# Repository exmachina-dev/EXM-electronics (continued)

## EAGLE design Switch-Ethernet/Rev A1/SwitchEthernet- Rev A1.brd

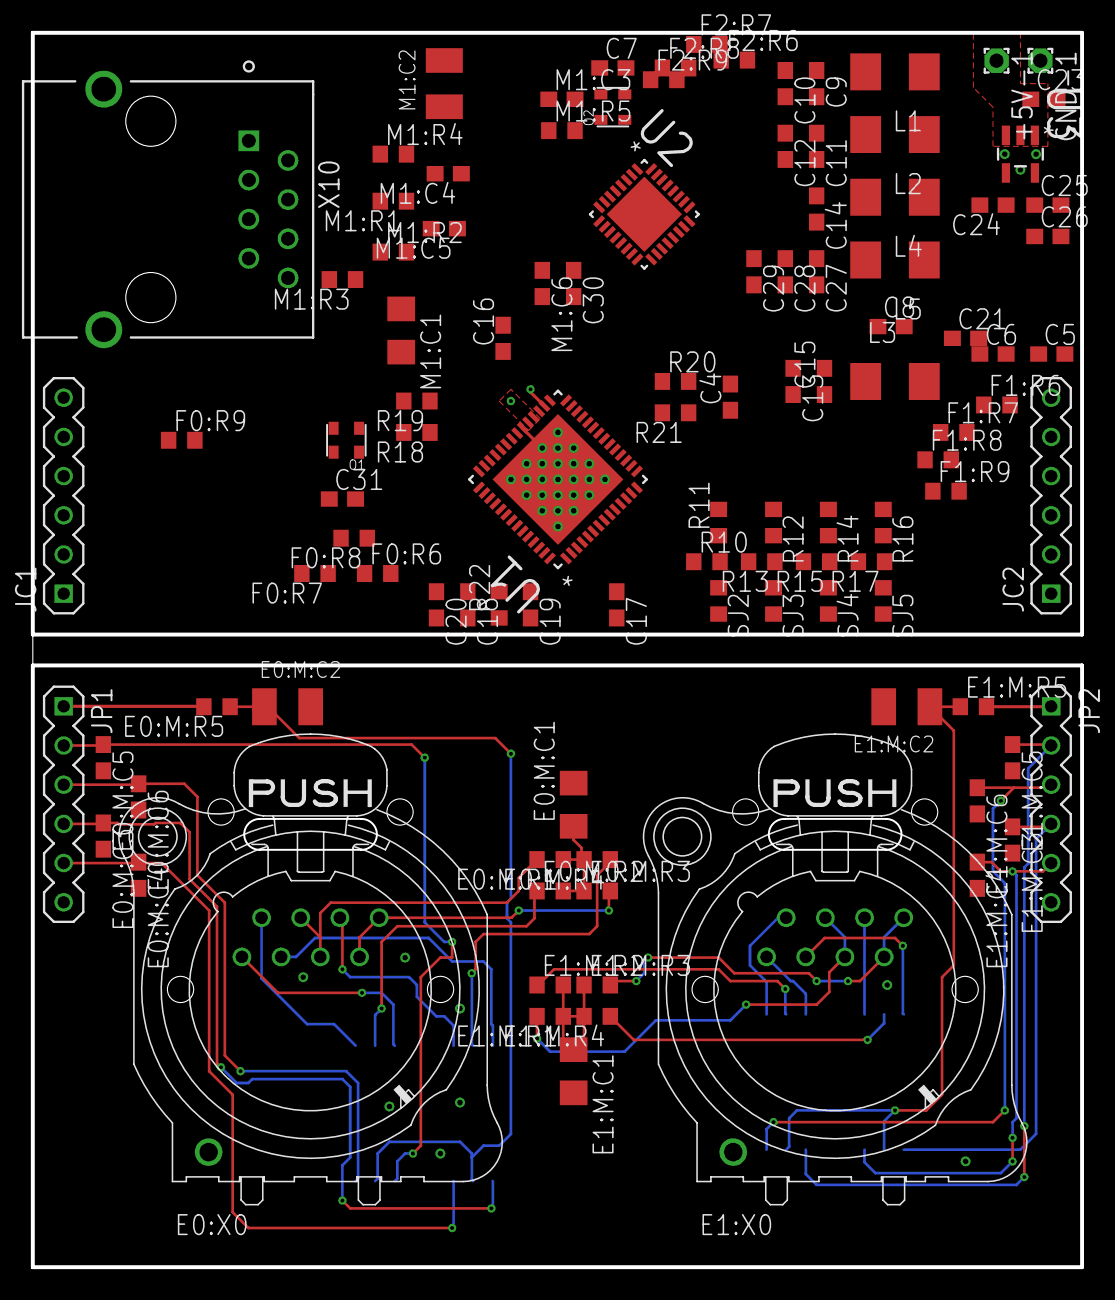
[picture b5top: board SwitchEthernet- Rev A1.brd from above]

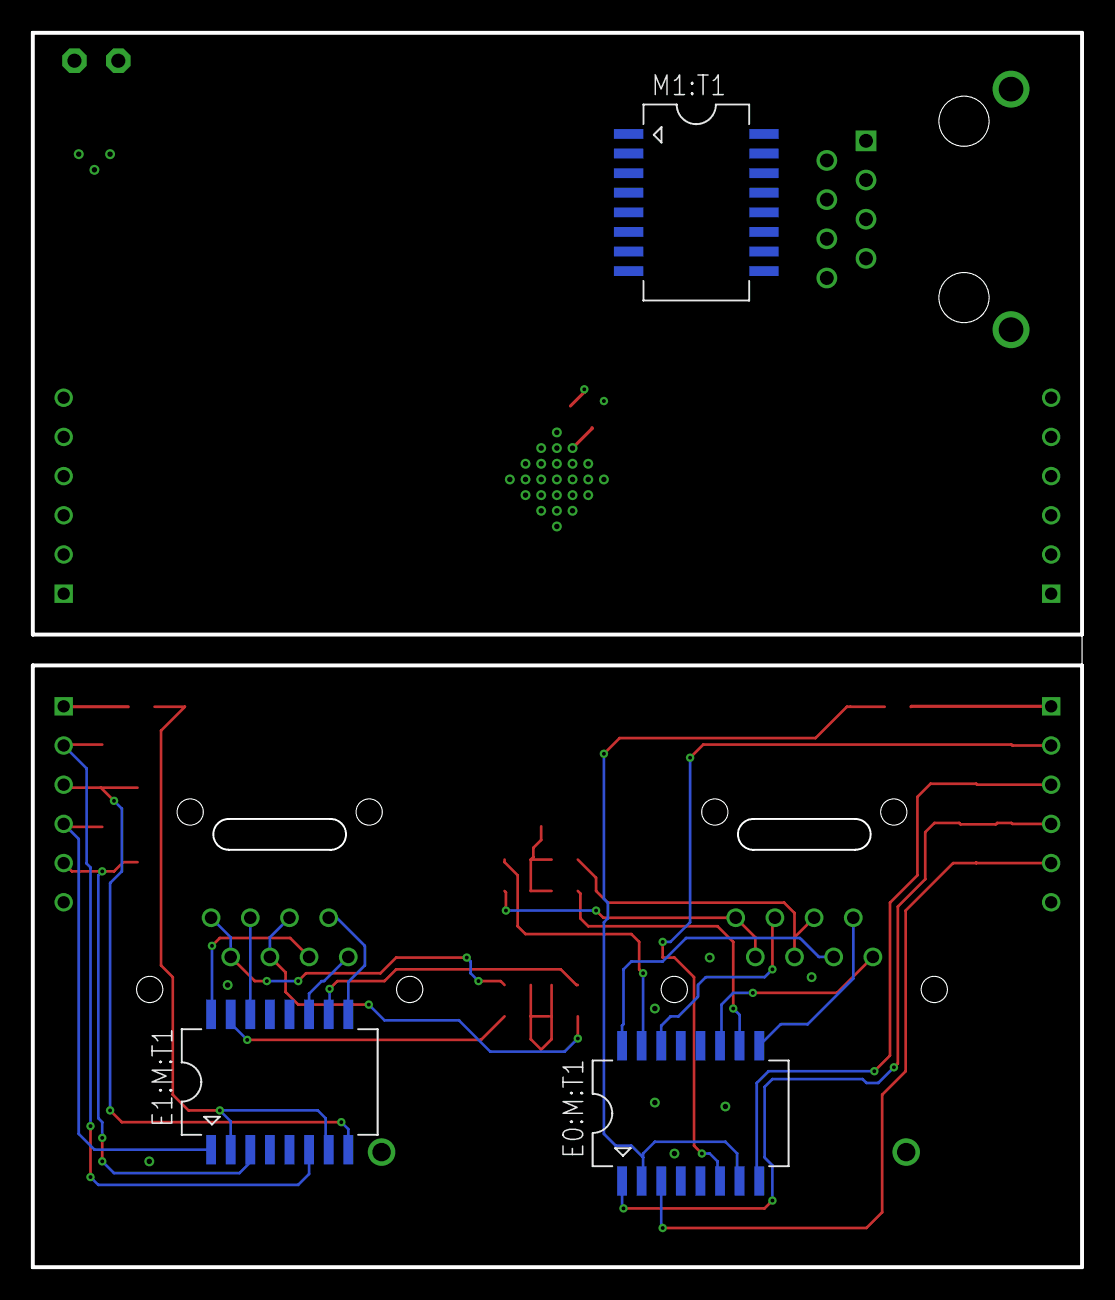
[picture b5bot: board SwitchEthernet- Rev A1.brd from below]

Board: 4 copper layers, 68.0 x 80.0 mm, 111 parts (3 on the bottom side), 90 nets.

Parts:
+5V-1: WIREPAD1,6/0,9; 1,6/0,9
C4, C9, C10, C11, C12, C13, C14, C15, C18: 4.7uF, 6.3V, 20%; C0603
C5, C6, C8, C16, C17, C19, C20: 0.1uF, 16V, 10%; C0603
C7: 0.1uF; C0603
C21, C31: 0.01uF, 6V, 10%; C0603
C23: 1uF, 16V; C0603
C24: 10nF, 50V; C0603
C25, C27: 4.7uF, 6.3V; C0603
C26, C28, C29, C30: 0.1uF, 16V; C0603
E0:M:C1, E1:M:C1: 1000pF, 2kV; C1206
E0:M:C2, E1:M:C2: .022uF; SMC_B
E0:M:C3, E0:M:C4, E0:M:C5, E0:M:C6, E1:M:C3, E1:M:C4, E1:M:C5, E1:M:C6: 15pF, 50V; C0603
E0:M:R1, E0:M:R2, E0:M:R3, E0:M:R4, E1:M:R1, E1:M:R2, E1:M:R3, E1:M:R4: 75; R0603
E0:M:R5, E1:M:R5: 10, 1/8W, 1%; R0603
E0:M:T1, E1:M:T1: 749010012
E0:X0, E1:X0: NE8FAV
F0:R6, F0:R7, F0:R8, F0:R9, F1:R6, F1:R7, F1:R8, F1:R9, F2:R6, F2:R7, F2:R8, F2:R9: 49.9, 1/8W, 1%; R0603
GND-1: WIREPAD1,6/0,9; 1,6/0,9
JC1, JC2: 1X06
JP1, JP2: 1X06
L1, L2, L3, L4, L5: 2.0A/0.05 DCR; L4532M
M1:C1: 1000pF, 2kV; C1206
M1:C2: .022uF; SMC_B
M1:C3, M1:C4, M1:C5, M1:C6: 15pF, 50V; C0603
M1:R1, M1:R2, M1:R3, M1:R4: 75; R0603
M1:R5: 10, 1/8W, 1%; R0603
M1:T1: 749010012
O1, O2: 25MHz; ADSM
R10, R11, R12, R13, R14, R15, R16, R17, R18, R19, R20, R21: 10K, 1/10W, 1%; R0603
R22: 12K4, 1%; R0603
SJ2, SJ3, SJ4, SJ5: O, DNI; R0603
U1: LAN9303-ABZJ; QFN50P800X800X100-57N
U2: LAN8710AI-EZK; QFN50P500X500X100-33N
U3: LP2992IM5-3.3; SOT95P284X122-5N
X10: 85505-5113; MOLEX_85505-5113

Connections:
+3V3: C4.1, C5.1, C6.1, C7.1, C8.1, C21.1, C25.1, C26.1, C31.1, L1.1, L2.1, L4.1, L5.1, O1.4, O2.4, R10.1, R12.1, R14.1, R16.1, R18.2, R19.2, R20.2, U1.9, U1.15, U1.23, U1.30, U1.32, U1.33, U3.5
+5V: +5V-1.1, C23.1, U3.1, U3.3
AVDD: C27.1, C28.1, C29.1, F2:R6.2, F2:R7.2, F2:R8.2, F2:R9.2, L5.2, M1:R5.2, U2.1, U2.27
DUPLEX_POL_0: R16.2, R17.1, SJ5.1
E0:M:N$1: E0:M:C2.+, E0:M:R5.1, E0:M:T1.2, E0:M:T1.7
E0:M:N$2: E0:M:R2.1, E0:M:T1.10
E0:M:N$3: E0:M:R4.1, E0:M:T1.15
E0:M:N$8: E0:M:C1.1, E0:M:R1.1, E0:M:R2.2, E0:M:R3.1, E0:M:R4.2
E0:N$1: E0:M:T1.11, E0:X0.1
E0:N$2: E0:M:T1.9, E0:X0.2
E0:N$3: E0:M:T1.16, E0:X0.3
E0:N$4: E0:M:T1.14, E0:X0.6
E0:N$5: E0:M:R1.2, E0:X0.4, E0:X0.5
E0:N$6: E0:M:R3.2, E0:X0.7, E0:X0.8
E1:M:N$1: E1:M:C2.+, E1:M:R5.1, E1:M:T1.2, E1:M:T1.7
E1:M:N$2: E1:M:R2.1, E1:M:T1.10
E1:M:N$3: E1:M:R4.1, E1:M:T1.15
E1:M:N$8: E1:M:C1.1, E1:M:R1.1, E1:M:R2.2, E1:M:R3.1, E1:M:R4.2
E1:N$1: E1:M:T1.11, E1:X0.1
E1:N$2: E1:M:T1.9, E1:X0.2
E1:N$3: E1:M:T1.16, E1:X0.3
E1:N$4: E1:M:T1.14, E1:X0.6
E1:N$5: E1:M:R1.2, E1:X0.4, E1:X0.5
E1:N$6: E1:M:R3.2, E1:X0.7, E1:X0.8
E2_1: M1:T1.11, X10.1
E2_2: M1:T1.9, X10.2
E2_3: M1:T1.16, X10.3
E2_4/5: M1:R1.2, X10.4, X10.5
E2_6: M1:T1.14, X10.6
E2_7/8: M1:R3.2, X10.7, X10.8
EE_SCL/SCL: R18.1, U1.36
EE_SDA/SDA: R19.1, U1.35
GND: C4.2, C5.2, C6.2, C7.2, C8.2, C9.2, C10.2, C11.2, C12.2, C13.2, C14.2, C15.2, C16.2, C17.2, C18.2, C19.2, C20.2, C21.2, C23.2, C24.2, C25.2, C26.2, C27.2, C28.2, C29.2, C30.2, C31.2, E0:M:C1.2, E0:M:C2.-, E0:M:C3.2, E0:M:C4.2, E0:M:C5.2, E0:M:C6.2, E0:X0.G, E1:M:C1.2, E1:M:C2.-, E1:M:C3.2, E1:M:C4.2, E1:M:C5.2, E1:M:C6.2, E1:X0.G, GND-1.1, JC1.6, JC2.6, JP1.6, JP2.6, M1:C1.2, M1:C2.-, M1:C3.2, M1:C4.2, M1:C5.2, M1:C6.2, O1.2, O2.2, R21.1, R22.1, SJ2.2, SJ3.2, SJ4.2, SJ5.2, U1.34, U1.57, U3.2, X10.M1, X10.M2
M1:N$1: M1:C2.+, M1:R5.1, M1:T1.2, M1:T1.7
M1:N$2: M1:R2.1, M1:T1.10
M1:N$3: M1:R4.1, M1:T1.15
M1:N$8: M1:C1.1, M1:R1.1, M1:R2.2, M1:R3.1, M1:R4.2
MDC: R21.2, U1.22, U2.17
MDIO: R20.1, U1.21, U2.16
unnamed: C24.1, U3.4
unnamed: R22.2, U1.49
unnamed: E0:M:C5.1, E0:M:T1.6, JP1.2
unnamed: E0:M:C6.1, E0:M:T1.8, JP1.3
unnamed: E0:M:C3.1, E0:M:T1.1, JP1.4
unnamed: E0:M:C4.1, E0:M:T1.3, JP1.5
unnamed: E1:M:R5.2, JP2.1
unnamed: E0:M:R5.2, JP1.1
unnamed: E1:M:C5.1, E1:M:T1.6, JP2.2
unnamed: E1:M:C6.1, E1:M:T1.8, JP2.3
unnamed: E1:M:C3.1, E1:M:T1.1, JP2.4
unnamed: E1:M:C4.1, E1:M:T1.3, JP2.5
P0_COL: U1.18, U2.15
P0_CRS: U1.19, U2.14
P0_INCLK: U1.8, U2.7
P0_IND0: U1.5, U2.11
P0_IND1: U1.4, U2.10
P0_IND2: U1.3, U2.9
P0_IND3: U1.2, U2.8
P0_INDV: U1.6, U2.26
P0_INER: U1.7, U2.13
P0_MODE0: R10.2, R11.1, SJ2.1
P0_MODE2: R14.2, R15.1, SJ4.1
P0_OUTCLK: U1.17, U2.20
P0_OUTD0/P0_MODE0: R11.2, U1.14, U2.22
P0_OUTD1/P0_MODE1: R13.2, U1.13
P0_OUTD2/P0_MODE2: R15.2, U1.12, U2.24
P0_OUTD3/DUPLEX_POL_0: R17.2, U1.11, U2.25
P0_OUTDV: U1.16, U2.21
PO_MODE1: R12.2, R13.1, SJ3.1
RXN0: F2:R9.1, M1:C4.1, M1:T1.3, U2.30
RXN1: F0:R9.1, JC1.5, U1.45
RXN2: F1:R9.1, JC2.5, U1.54
RXP0: F2:R8.1, M1:C3.1, M1:T1.1, U2.31
RXP1: F0:R8.1, JC1.4, U1.46
RXP2: F1:R8.1, JC2.4, U1.53
TXN0: F2:R7.1, M1:C6.1, M1:T1.8, U2.28
TXN1: F0:R7.1, JC1.3, U1.42
TXN2: F1:R7.1, JC2.3, U1.1
TXP0: F2:R6.1, M1:C5.1, M1:T1.6, U2.29
TXP1: F0:R6.1, JC1.2, U1.43
TXP2: F1:R6.1, JC2.2, U1.56
VDD18CORE: C15.1, C16.1, C17.1, L3.1, U1.10, U1.31
VDD18PLL: C13.1, L3.2, U1.41
VDD18TX: C18.1, C19.1, C20.1, U1.48, U1.51
VDD33A1: C9.1, C10.1, F0:R6.2, F0:R7.2, F0:R8.2, F0:R9.2, JC1.1, L1.2, U1.44, U1.47
VDD33A2: C11.1, C12.1, F1:R6.2, F1:R7.2, F1:R8.2, F1:R9.2, JC2.1, L2.2, U1.52, U1.55
VDD33BIAS: C14.1, L4.2, U1.50
VDDIO: C30.1, U2.12
XI: O1.3, U1.39
XTAL1/CLKIN: O2.3, U2.5
